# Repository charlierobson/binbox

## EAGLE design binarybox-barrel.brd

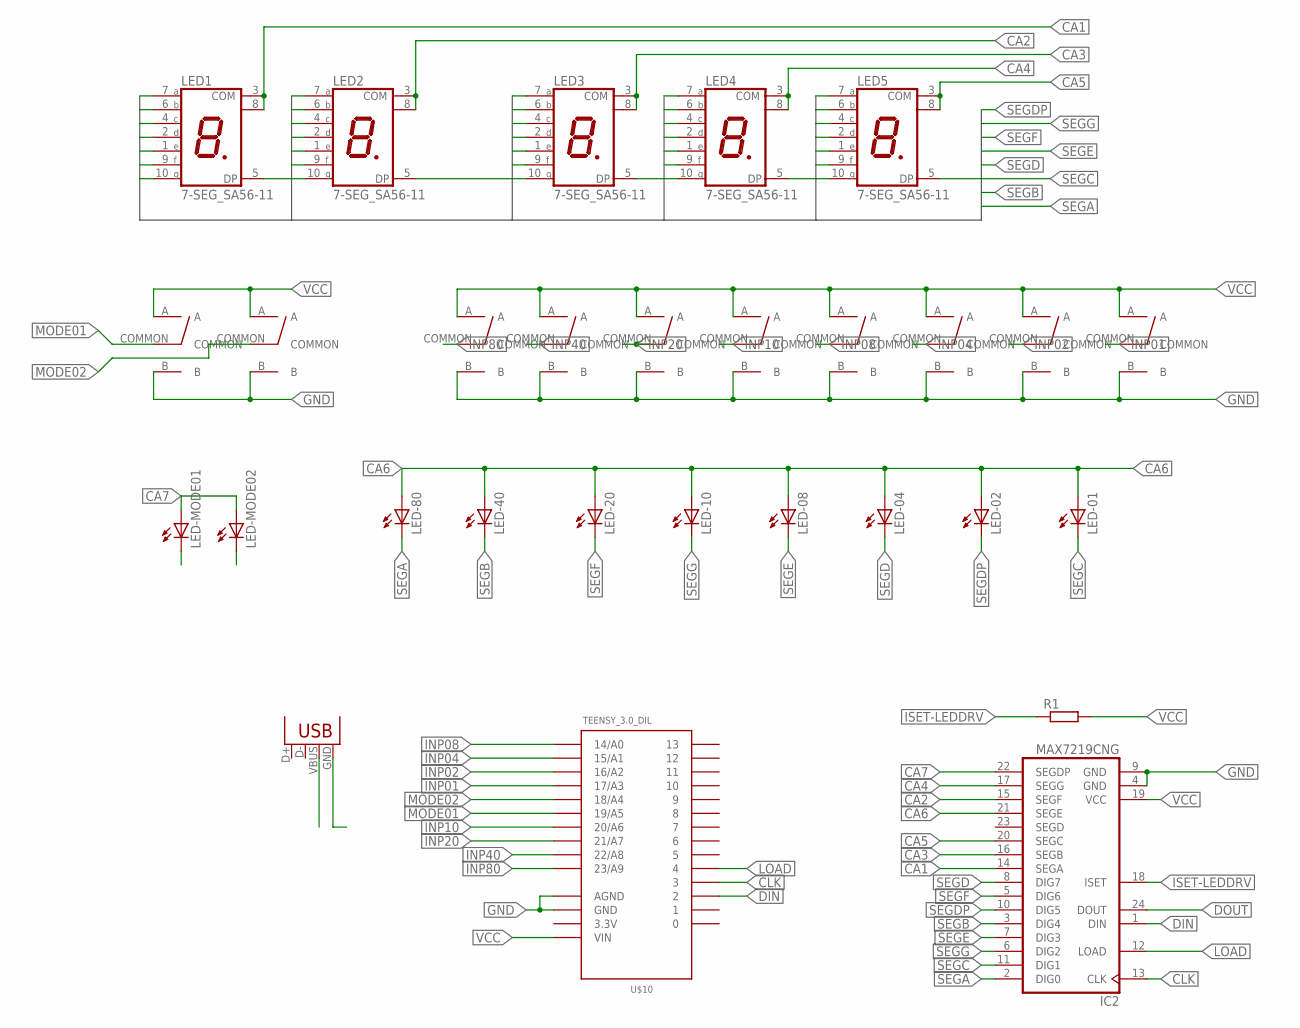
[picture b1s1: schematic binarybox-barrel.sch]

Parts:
IC2: MAX7219CNG; DIL24-3
LED1, LED2, LED3, LED4, LED5: 7-SEG_SA56-11; SA56-11
LED-01, LED-02, LED-04, LED-08, LED-10, LED-20, LED-40, LED-80: LED5MM
LED-MODE01, LED-MODE02: LED5MM
R1: R-EU_0207/10; 0207/10
U$1, U$2, U$3, U$4, U$5, U$6, U$7, U$8, U$11, U$13: ARROW-AB-SWITCH; 333-333
U$10: TEENSY_3.0_DIL; TEENSY3-DIL
X1: USBPTH; USB-B-PTH

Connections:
3.3V: U$10.3.3V
CA1: IC2.14 (SEGA), LED1.3 (COM), LED1.8 (COM)
CA2: IC2.15 (SEGF), LED2.3 (COM), LED2.8 (COM)
CA3: IC2.16 (SEGB), LED3.3 (COM), LED3.8 (COM)
CA4: IC2.17 (SEGG), LED4.3 (COM), LED4.8 (COM)
CA5: IC2.20 (SEGC), LED5.3 (COM), LED5.8 (COM)
CA6: IC2.21 (SEGE), LED-01.A, LED-02.A, LED-04.A, LED-08.A, LED-10.A, LED-20.A, LED-40.A, LED-80.A
CA7: IC2.22 (SEGDP), LED-MODE01.A, LED-MODE02.A
CLK: IC2.13 (CLK), U$10.3
DIN: IC2.1 (DIN), U$10.2
DOUT: IC2.24 (DOUT)
GND: IC2.4 (GND), IC2.9 (GND), U$1.B, U$2.B, U$3.B, U$4.B, U$5.B, U$6.B, U$7.B, U$8.B, U$10.AGND, U$10.GND, U$11.B, U$13.B, X1.GND
INP01: U$8.COMMON, U$10.17/A3
INP02: U$7.COMMON, U$10.16/A2
INP04: U$6.COMMON, U$10.15/A1
INP08: U$5.COMMON, U$10.14/A0
INP10: U$4.COMMON, U$10.20/A6
INP20: U$3.COMMON, U$10.21/A7
INP40: U$2.COMMON, U$10.22/A8
INP80: U$1.COMMON, U$10.23/A9
ISET-LEDDRV: IC2.18 (ISET), R1.1
LOAD: IC2.12 (LOAD), U$10.4
MODE01: U$10.19/A5, U$11.COMMON
MODE02: U$10.18/A4, U$13.COMMON
SEGA: IC2.2 (DIG0), LED1.7 (A), LED2.7 (A), LED3.7 (A), LED4.7 (A), LED5.7 (A), LED-80.K (C)
SEGB: IC2.3 (DIG4), LED1.6 (B), LED2.6 (B), LED3.6 (B), LED4.6 (B), LED5.6 (B), LED-40.K (C)
SEGC: IC2.11 (DIG1), LED1.4 (C), LED2.4 (C), LED3.4 (C), LED4.4 (C), LED5.4 (C), LED-01.K (C), LED-MODE01.K (C)
SEGD: IC2.8 (DIG7), LED1.2 (D), LED2.2 (D), LED3.2 (D), LED4.2 (D), LED5.2 (D), LED-04.K (C)
SEGDP: IC2.10 (DIG5), LED1.5 (DP), LED2.5 (DP), LED3.5 (DP), LED4.5 (DP), LED5.5 (DP), LED-02.K (C), LED-MODE02.K (C)
SEGE: IC2.7 (DIG3), LED1.1 (E), LED2.1 (E), LED3.1 (E), LED4.1 (E), LED5.1 (E), LED-08.K (C)
SEGF: IC2.5 (DIG6), LED1.9 (F), LED2.9 (F), LED3.9 (F), LED4.9 (F), LED5.9 (F), LED-20.K (C)
SEGG: IC2.6 (DIG2), LED1.10 (G), LED2.10 (G), LED3.10 (G), LED4.10 (G), LED5.10 (G), LED-10.K (C)
VCC: IC2.19 (VCC), R1.2, U$1.A, U$2.A, U$3.A, U$4.A, U$5.A, U$6.A, U$7.A, U$8.A, U$10.VIN, U$11.A, U$13.A, X1.VBUS

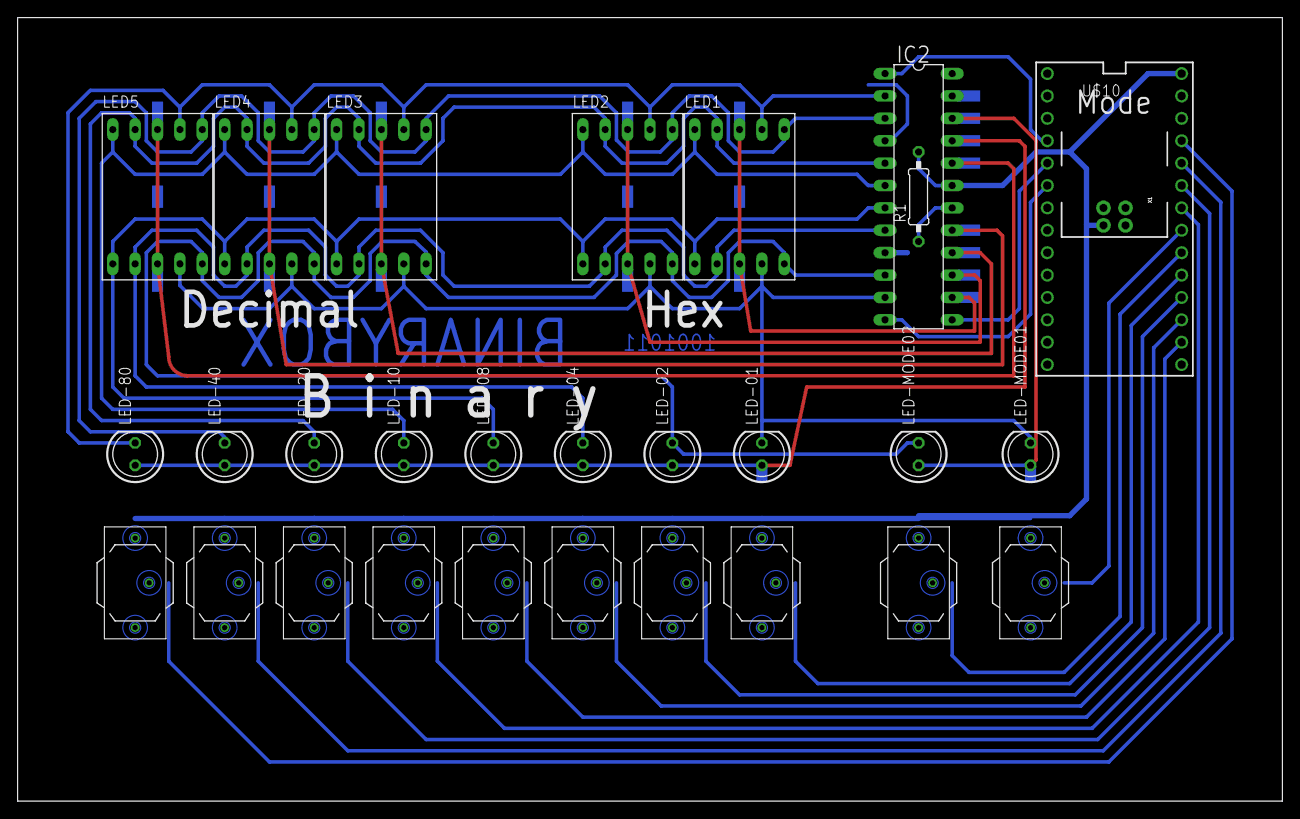
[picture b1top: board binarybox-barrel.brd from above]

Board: 2 copper layers, 143.5 x 88.9 mm, 29 parts (0 on the bottom side), 31 nets.

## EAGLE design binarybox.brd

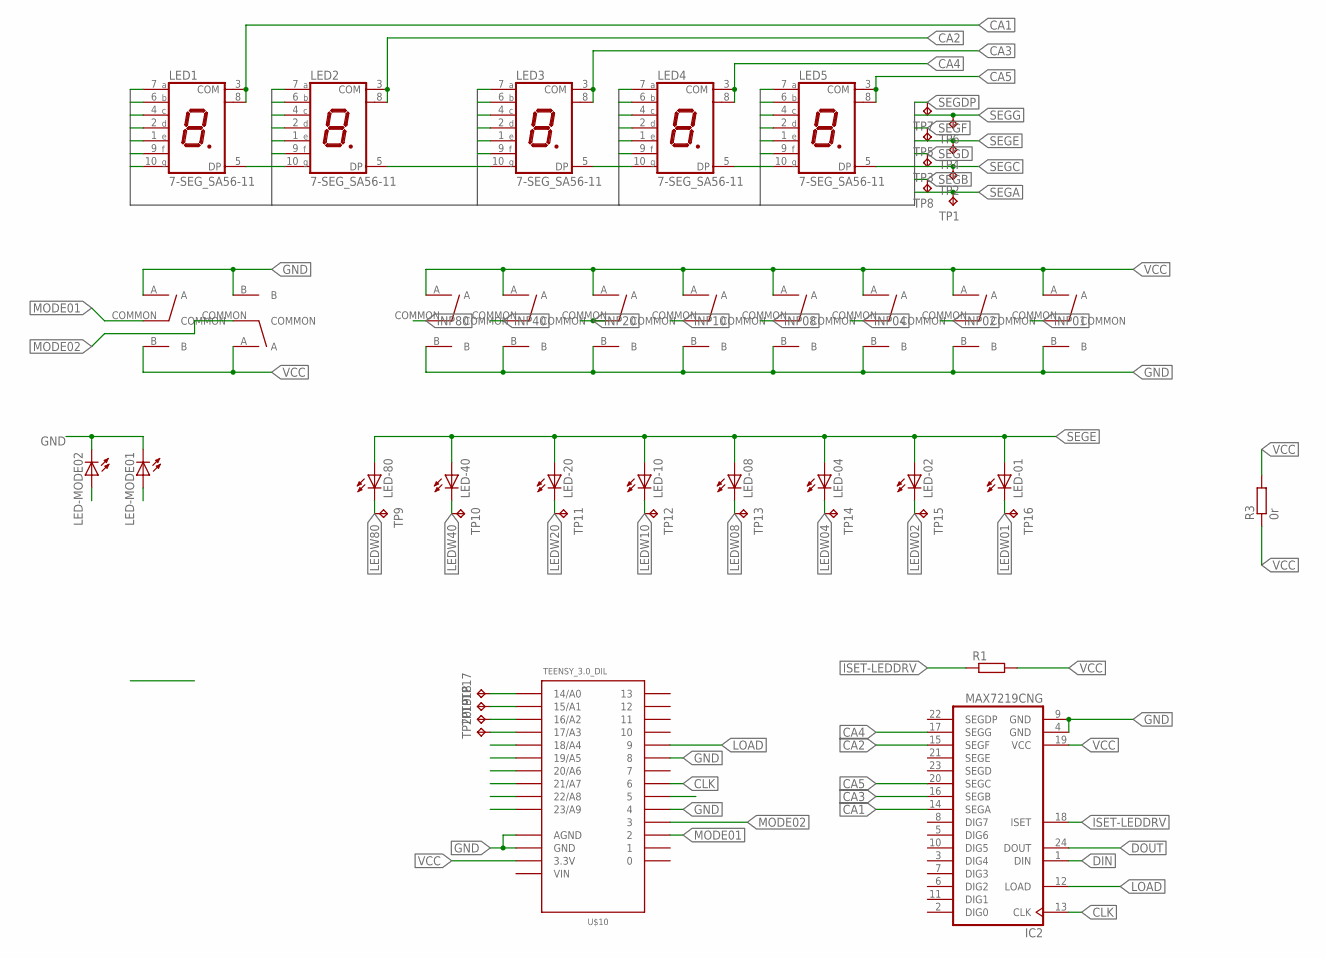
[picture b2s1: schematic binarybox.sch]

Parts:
IC2: MAX7219CNG; DIL24-3
LED1, LED2, LED3, LED4, LED5: 7-SEG_SA56-11; SA56-11
LED-01, LED-02, LED-04, LED-08, LED-10, LED-20, LED-40, LED-80: LED5MM
LED-MODE01, LED-MODE02: LED5MM
R1: R-EU_0207/10; 0207/10
R3: 0r; 0207/10
TP1, TP2, TP3, TP4, TP5, TP6, TP7, TP8, TP9, TP10, TP11, TP12, TP13, TP14, TP15, TP16, TP17, TP18, TP19, TP20: TPB1,27; B1,27
U$1, U$2, U$3, U$4, U$5, U$6, U$7, U$8, U$11, U$13: ARROW-AB-SWITCH; 333-333
U$10: TEENSY_3.0_DIL; TEENSY3-DIL

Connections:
CA1: IC2.14 (SEGA), LED1.3 (COM), LED1.8 (COM)
CA2: IC2.15 (SEGF), LED2.3 (COM), LED2.8 (COM)
CA3: IC2.16 (SEGB), LED3.3 (COM), LED3.8 (COM)
CA4: IC2.17 (SEGG), LED4.3 (COM), LED4.8 (COM)
CA5: IC2.20 (SEGC), LED5.3 (COM), LED5.8 (COM)
CLK: IC2.13 (CLK), U$10.6
DIN: IC2.1 (DIN), U$10.5
DOUT: IC2.24 (DOUT)
GND: IC2.4 (GND), IC2.9 (GND), LED-MODE01.K (C), LED-MODE02.K (C), U$1.B, U$2.B, U$3.B, U$4.B, U$5.B, U$6.B, U$7.B, U$8.B, U$10.4, U$10.8, U$10.AGND, U$10.GND, U$11.A, U$13.B
INP01: U$8.COMMON
INP02: U$7.COMMON
INP04: U$6.COMMON
INP08: U$5.COMMON
INP10: U$4.COMMON
INP20: U$3.COMMON
INP40: U$2.COMMON
INP80: U$1.COMMON
ISET-LEDDRV: IC2.18 (ISET), R1.1
LEDMODE01: LED-MODE02.A
LEDMODE02: LED-MODE01.A
LEDW01: LED-01.K (C), TP16.TP
LEDW02: LED-02.K (C), TP15.TP
LEDW04: LED-04.K (C), TP14.TP
LEDW08: LED-08.K (C), TP13.TP
LEDW10: LED-10.K (C), TP12.TP
LEDW20: LED-20.K (C), TP11.TP
LEDW40: LED-40.K (C), TP10.TP
LEDW80: LED-80.K (C), TP9.TP
LOAD: IC2.12 (LOAD), U$10.9
MODE01: U$10.2, U$11.COMMON
MODE02: U$10.3, U$13.COMMON
unnamed: TP17.TP, U$10.14/A0
unnamed: TP18.TP, U$10.15/A1
unnamed: TP19.TP, U$10.16/A2
unnamed: TP20.TP, U$10.17/A3
SEGA: LED1.7 (A), LED2.7 (A), LED3.7 (A), LED4.7 (A), LED5.7 (A), TP1.TP
SEGB: LED1.6 (B), LED2.6 (B), LED3.6 (B), LED4.6 (B), LED5.6 (B), TP8.TP
SEGC: LED1.4 (C), LED2.4 (C), LED3.4 (C), LED4.4 (C), LED5.4 (C), TP2.TP
SEGD: LED1.2 (D), LED2.2 (D), LED3.2 (D), LED4.2 (D), LED5.2 (D), TP3.TP
SEGDP: LED1.5 (DP), LED2.5 (DP), LED3.5 (DP), LED4.5 (DP), LED5.5 (DP), TP7.TP
SEGE: LED1.1 (E), LED2.1 (E), LED3.1 (E), LED4.1 (E), LED5.1 (E), LED-01.A, LED-02.A, LED-04.A, LED-08.A, LED-10.A, LED-20.A, LED-40.A, LED-80.A, TP4.TP
SEGF: LED1.9 (F), LED2.9 (F), LED3.9 (F), LED4.9 (F), LED5.9 (F), TP5.TP
SEGG: LED1.10 (G), LED2.10 (G), LED3.10 (G), LED4.10 (G), LED5.10 (G), TP6.TP
VCC: IC2.19 (VCC), R1.2, R3.1, R3.2, U$1.A, U$2.A, U$3.A, U$4.A, U$5.A, U$6.A, U$7.A, U$8.A, U$10.3.3V, U$11.B, U$13.A
VIN: U$10.VIN

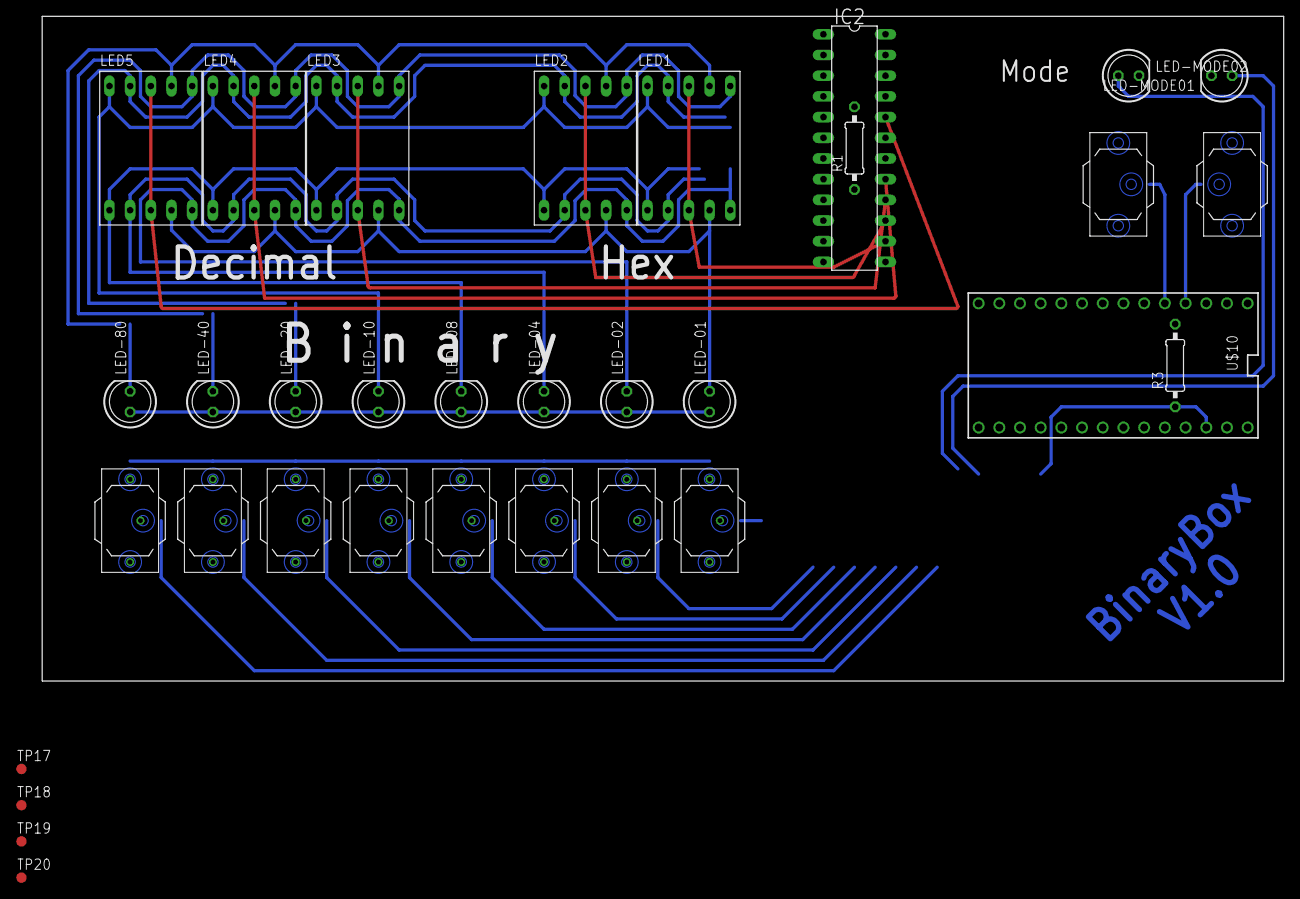
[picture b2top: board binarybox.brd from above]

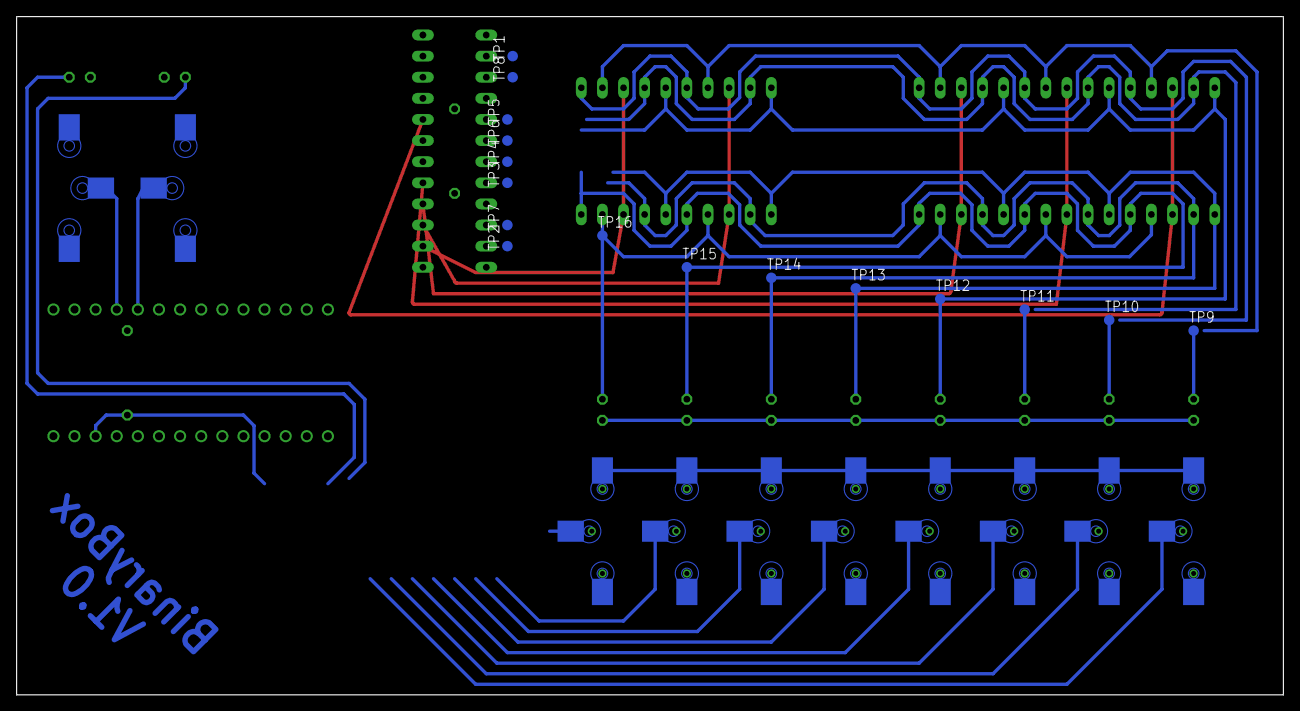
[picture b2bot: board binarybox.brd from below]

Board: 2 copper layers, 152.4 x 81.6 mm, 49 parts (16 on the bottom side), 33 nets.

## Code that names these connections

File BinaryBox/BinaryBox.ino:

#include "XControl.h"

#include "game1.h"
#include "game2.h"

/*

  80
0    0
2    8
  20
1    4
0    0
  01    04
  
 */


XControl* lc;

// teensy pins
#define TEENSY_DIN 2
#define TEENSY_CLK 3
#define TEENSY_LOAD 4

#define INP80 23
#define INP40 22
#define INP20 21
#define INP10 20

#define INPMO 19
#define INPAC 18

#define INP01 17
#define INP02 16
#define INP04 15
#define INP08 14

// bit numbers for LEDs
#define LED_MODE 1
#define LED_ACTN 5

#define LED_H80 0
#define LED_H01 1
#define LED_H10 2
#define LED_H08 3
#define LED_H40 4
#define LED_H02 5
#define LED_H20 6
#define LED_H04 7

// switch state
#define SS_OFF      0
#define SS_JUSTOFF  1
#define SS_JUSTON   2
#define SS_ON       3

#define SWITCHISON(x) ((switchStates[x]&2)==2)

byte debouncedSwitches[10];
byte switchStates[10];

// indices into debounced switch array
#define SN_MODE 8
#define SN_ACT 9

// teensy pin mapping to debounced switch array entry
int switchPinMap[10] =
{
  INP80, INP40, INP20, INP10,
  INP08, INP04, INP02, INP01,
  INPMO, INPAC
};

// 7-seg led bitmaps

byte characterBitmaps[16] = 
{
  0b11011011,
  0b01001000,
  0b10111001,
  0b11101001,
  0b01101010,
  0b11100011,
  0b11110011,
  0b11001000,
  0b11111011,
  0b11101010,

  0b11111010,
  0b01110011,
  0b10010011,
  0b01111001,
  0b10110011,
  0b10110010
};

byte yes[3] = 
{
  0b01101010, 
  0b10110011,
  0b11100011
};

byte cache[8];
byte data[8] = { 0x4, 0x4, 0x4, 0x4, 0x4, 0x4, 0x4, 0x04 };

int gt;

void setup()
{
  Serial.begin(19200);

  randomSeed(analogRead(0));
  
  pinMode(5,OUTPUT); // test pin
  
  pinMode(13,OUTPUT);

  for (int i = 14; i < 24; ++i)
  {
    pinMode(i, INPUT);
  }

  lc = new XControl(TEENSY_DIN,TEENSY_CLK,TEENSY_LOAD);

  // initialise debouncing/states to reflect ON or OFF
  for (int i = 0; i < 10; ++i)
  {
    debouncedSwitches[i] = digitalRead(switchPinMap[i]) ? 0xff : 0;
    switchStates[i] = debouncedSwitches[i] & SS_ON;
  }
}

void updateSwitches(void)
{
  byte v, before, after;
  
  for (int i = 0; i < 10; ++i)
  {
    v = debouncedSwitches[i];
    v <<= 1;
    v |= digitalRead(switchPinMap[i]);
    debouncedSwitches[i] = v;

    before = (v & 0b11100000) == 0b11100000;
    after  = (v & 0b00000111) == 0b00000111;
    switchStates[i] = before + (after << 1);
  }
}

bool actFlipped(void)
{
  return switchStates[SN_ACT] == SS_JUSTON;
}

byte collectBinary(void)
{
  int n = 0;
  for (int i = 0; i < 8; ++i)
  {
    n <<= 1;
    n |= SWITCHISON(i);
  }
  return n;
}

void outputBinary(byte n)
{
  for (int i = 0; i < 8; ++i)
    data[i] &= 0b11111011;

  if (n & 0x80) data[LED_H80] |= 4;
  if (n & 0x40) data[LED_H40] |= 4;
  if (n & 0x20) data[LED_H20] |= 4;
  if (n & 0x10) data[LED_H10] |= 4;
  if (n & 0x08) data[LED_H08] |= 4;
  if (n & 0x04) data[LED_H04] |= 4;
  if (n & 0x02) data[LED_H02] |= 4;
  if (n & 0x01) data[LED_H01] |= 4;
}

void outputToModule(byte moduleMask, byte bitmap)
{
  for (int i = 0; i < 8; ++i)
  {
    data[i] &= ~moduleMask;
    if (bitmap & 0x80)
      data[i] |= moduleMask;
    bitmap <<= 1;
  }
}

void outputDigit(byte moduleMask, byte digit)
{
  unsigned char bitmap = characterBitmaps[digit];
  outputToModule(moduleMask, bitmap);
}

void outputDecimal(byte n)
{
  int hundreds = n / 100;
  n -= hundreds * 100;
  outputDigit(0x80, hundreds);

  int tens = n / 10;
  n -= tens * 10;
  outputDigit(0x40, tens);
  
  outputDigit(0x20, n);
}

void outputHex(byte n)
{
  outputDigit(0x10, n >> 4);
  outputDigit(0x08, n & 15);
}

void clearModule(byte mask)
{
  for (int i = 0; i < 8; ++i)
  {
    data[i] &= mask;
  }
}

void lightMode(bool mode)
{
  data[LED_H01] = data[LED_H01] & ~2;
  data[LED_H01] |= mode ? 2 : 0;
}

void lightAction(bool action)
{
  data[LED_H02] = data[LED_H02] & ~2;
  data[LED_H02] |= action ? 2 : 0;
}

void cacheData(void)
{
  memcpy(cache, data, 8);
}

void restoreData(void)
{
  memcpy(data, cache, 8);
}

void flashYes(void)
{
  cacheData();

  for (int i = 0; i < 12; ++i)
  {
    clearModule(0b00011111);
    lc->updateDisplay(data);
    delay(100);
    outputToModule(0x80, yes[0]);
    outputToModule(0x40, yes[1]);
    outputToModule(0x20, yes[2]);
    lc->updateDisplay(data);
    delay(100);
  }

  restoreData();
  lc->updateDisplay(data);
}




//

void* play_begin(void)
{
  return (void*)play_loop;
}

void* play_loop(void)
{
  int binary = collectBinary();
  outputBinary(binary);
  outputDecimal(binary);  
  outputHex(binary);

  return (void*)play_loop;
}

typedef void*(*WFN)(void);


extern void* game1_begin(void);
extern void* game2_begin(void);

int mode = 0;       // play mode. 1 = game
int loopCount = 31; // we want the buttons to be read on the first iteration

WFN modes[3] = { play_begin, game1_begin, game2_begin };
WFN fn = (WFN)modes[0];

byte randy;

void loop()
{
  loopCount = (loopCount + 1) & 31;
  if (loopCount == 0)
  {
    // shonky game timer, counts in milliseconds, _very_ roughly
    gt += 7;
    
    // about 7.5ms update rate
    digitalWrite(5, !digitalRead(5));
    updateSwitches();

    // switch mode when mode switch makes a positive edge transition
    if (switchStates[SN_MODE] == SS_JUSTON)
    {
      ++mode;
      mode %= sizeof(modes);
  
      fn = modes[mode];
    }
  }

  fn = (WFN)fn();

  lc->updateDisplay(data);
}

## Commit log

2016-05-11 rework - removing io expander
2016-05-18 cleaned up usb board and arduino sketch
2016-05-19 added improved button state detection and debouncing, first step toward game mode
2016-05-24 first cut of game, not bad but need to use an enum for the operating modes
2016-05-25 game2

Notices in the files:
parts and their libraries:
SparkFun: Licensing: CC v3.0 Share-Alike You are welcome to use this library for commercial purposes.
